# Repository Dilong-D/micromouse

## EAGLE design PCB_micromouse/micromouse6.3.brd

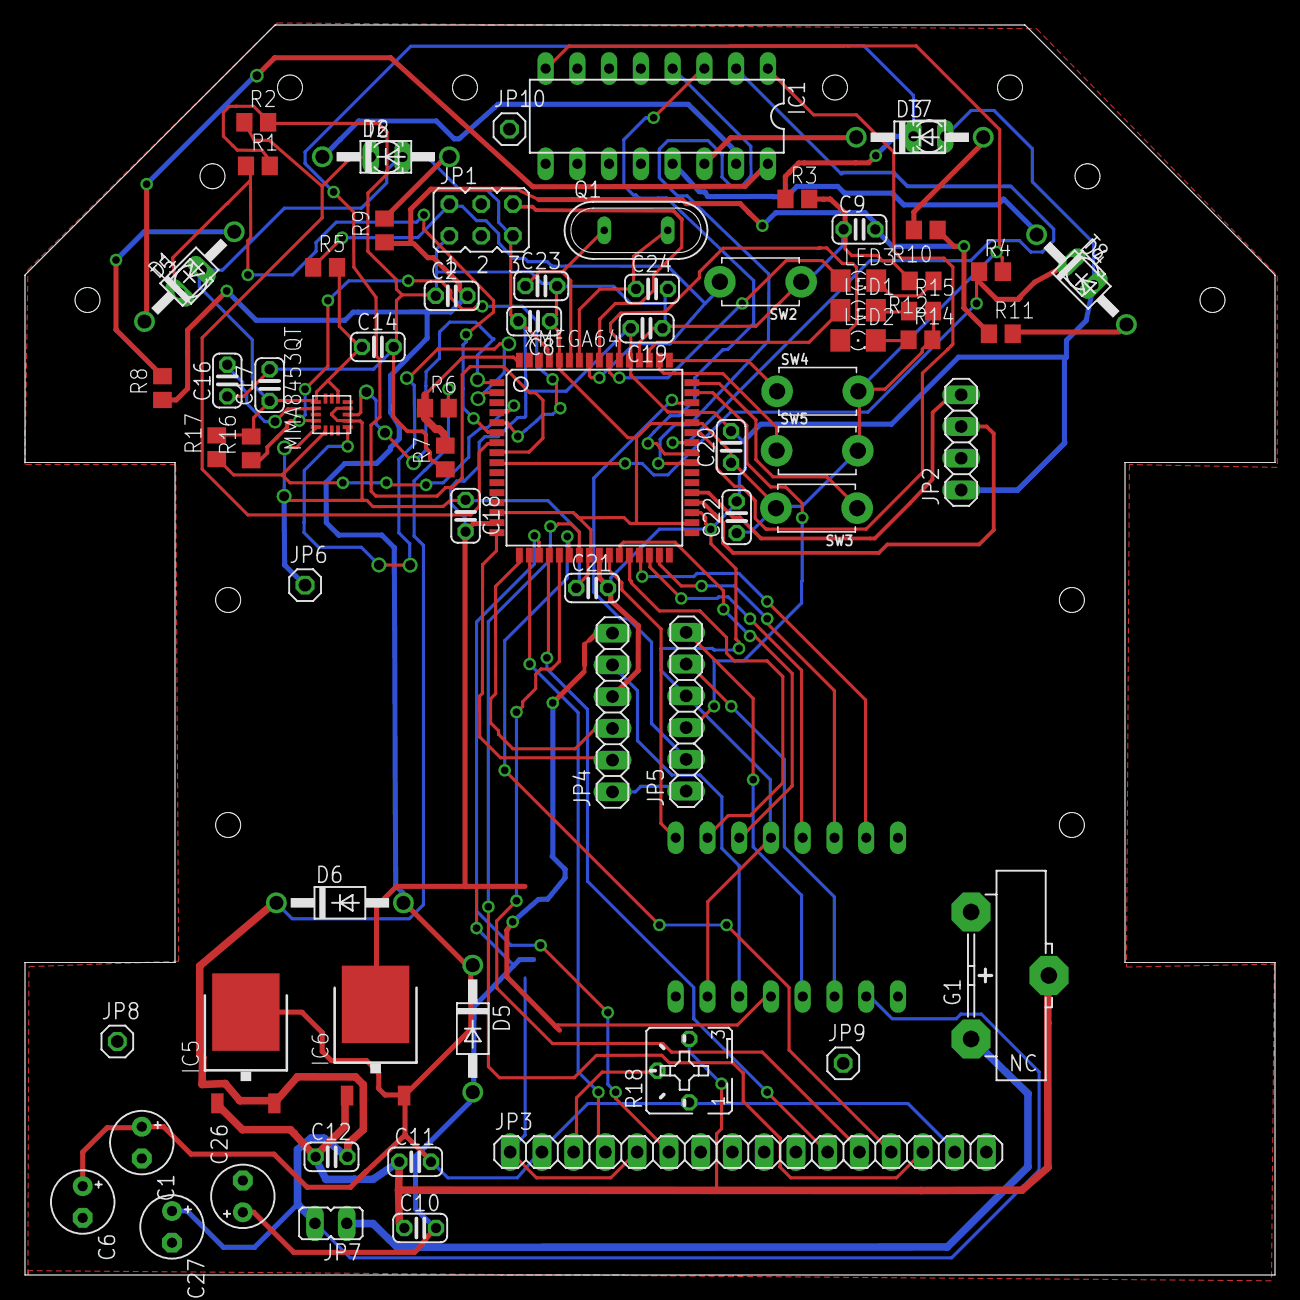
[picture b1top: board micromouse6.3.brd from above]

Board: 2 copper layers, 100.0 x 100.0 mm, 72 parts (0 on the bottom side), 63 nets.

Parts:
ACC1: MMA8453QT
C1, C6, C26, C27: E2,5-5
C2, C9: C025-024X044
C8, C11, C12, C18, C19, C20, C21, C22: 100n; C025-024X044
C10: 10μ; C025-024X044
C14: 4,7μ; C025-024X044
C16, C17: 0.1μ; C025-024X044
C23, C24: 15p; C025-024X044
D1, D2, D3, D4: sfh4550; DO41-10
D5, D6: 1N4004; DO41-10
G1: 1V60R
IC1: ULN2003AN; DIL16
IC5, IC6: LM1117IDTX-3.3; TO252
JP1: JP3Q
JP2: 1X04
JP3: 1X16
JP4, JP5: 1X06
JP6, JP8, JP9, JP10: 1X01
JP7: JP1
LED1, LED2, LED3: 1206
Q1: QS
R1, R2, R3, R4: 1k; R0805
R5, R7: 10k; R0805
R6: 20k; R0805
R8, R9, R10, R11: 10; R0805
R12, R14, R15: 220; R0805
R16, R17: 4.7k; R0805
R18: B25P
SW2, SW3, SW4, SW5: TACT_PANA-EVQ
T5, T6, T7, T8: BPX81
U$1: POLULU713
XMEGA64: TQFP64

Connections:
AIN: R6.1, R7.2, XMEGA64.64
A_IN1: U$1.P$14, XMEGA64.27
A_IN2: U$1.P$15, XMEGA64.28
A_PWM: U$1.P$16, XMEGA64.26
B_IN1: U$1.P$12, XMEGA64.30
B_IN2: U$1.P$11, XMEGA64.31
B_PWM: U$1.P$10, XMEGA64.29
CLK: JP1.2, R5.1, SW2.P$2, XMEGA64.57
CLK_: JP2.3, XMEGA64.36
DATA: JP1.6, XMEGA64.56
FOTRA1: R1.1, T5.E, XMEGA64.6
FOTRA2: R2.1, T6.E, XMEGA64.7
FOTRA3: R3.1, T7.E, XMEGA64.8
FOTRA4: R4.1, T8.E, XMEGA64.9
GND: ACC1.GND1, ACC1.GND2, ACC1.GND3, C1.-, C2.1, C6.-, C8.1, C9.1, C10.1, C11.1, C12.1, C14.2, C16.1, C17.2, C18.1, C19.1, C20.1, C21.1, C22.1, C23.2, C24.2, C26.-, C27.-, G1.-, IC1.8, IC5.1, IC6.1, JP1.1, JP2.2, JP3.1, JP3.5, JP3.16, JP4.1, JP5.1, JP6.1, JP8.1, JP9.1, JP10.1, R1.2, R2.2, R3.2, R4.2, R7.1, R12.2, R14.2, R15.2, R18.E, SW2.P$1, SW3.P$2, SW4.P$2, SW5.P$2, U$1.P$1, U$1.P$8, U$1.P$9, XMEGA64.14, XMEGA64.24, XMEGA64.34, XMEGA64.44, XMEGA64.52, XMEGA64.60
INT1: ACC1.INT1, XMEGA64.1
INT2: ACC1.INT2, XMEGA64.2
L_DIAG: IC1.1, XMEGA64.43
L_FROM: IC1.2, XMEGA64.42
MA_OUT1: JP4.5, U$1.P$3
MA_OUT2: JP4.6, U$1.P$4
MB_OUT1: JP5.5, U$1.P$6
MB_OUT2: JP5.6, U$1.P$5
unnamed: LED1.A, XMEGA64.51
unnamed: D2.A, R9.2
unnamed: D1.A, R8.2
unnamed: D1.C, IC1.16
unnamed: D2.C, IC1.15
unnamed: D4.A, R11.2
unnamed: D3.C, IC1.14
unnamed: D3.A, R10.2
unnamed: D4.C, IC1.13
unnamed: LED2.A, XMEGA64.54
unnamed: JP3.13, XMEGA64.22
unnamed: JP3.4, XMEGA64.18
unnamed: JP3.6, XMEGA64.19
unnamed: LED3.A, XMEGA64.55
unnamed: C23.1, Q1.1, XMEGA64.59
unnamed: SW3.P$1, XMEGA64.48
unnamed: G1.+, JP7.1
unnamed: JP3.3, R18.S
unnamed: C24.1, Q1.2, XMEGA64.58
unnamed: SW4.P$1, XMEGA64.49
unnamed: SW5.P$1, XMEGA64.50
unnamed: JP3.11, XMEGA64.20
unnamed: LED3.C, R12.1
unnamed: LED2.C, R14.1
unnamed: LED1.C, R15.1
unnamed: JP2.4, XMEGA64.37
unnamed: ACC1.BYP, C16.2
unnamed: JP3.12, XMEGA64.21
unnamed: JP3.14, XMEGA64.23
OUTA1: JP4.2, XMEGA64.16
OUTA2: JP4.3, XMEGA64.17
OUTB1: JP5.2, XMEGA64.46
OUTB2: JP5.3, XMEGA64.47
R_DIAG: IC1.3, XMEGA64.41
R_FRONT: IC1.4, XMEGA64.40
SCL: ACC1.SCL, R16.1, XMEGA64.5
SDA: ACC1.SDA, R17.1, XMEGA64.4
VCC3: ACC1.VDD, ACC1.VDDIO, C8.2, C10.2, C14.1, C17.1, C18.2, C19.2, C20.2, C21.2, C22.2, C26.+, D5.A, IC6.TAB, JP1.5, JP2.1, JP4.4, JP5.4, R5.2, R16.2, R17.2, T5.C, T6.C, T7.C, T8.C, U$1.P$2, U$1.P$13, XMEGA64.15, XMEGA64.25, XMEGA64.35, XMEGA64.45, XMEGA64.53, XMEGA64.61
VCC5: C1.+, C2.2, C6.+, C9.2, C11.2, D5.C, D6.A, IC5.TAB, IC6.2, JP3.2, JP3.15, R8.1, R9.1, R10.1, R11.1, R18.A
VCC7: C12.2, C27.+, D6.C, IC5.2, JP7.2, R6.2, U$1.P$7

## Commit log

2017-07-27 MATLAB: skrypty do odczytu bluetoothKod:Micromouse jezdzi, pozycjonuje sie wzgledem scianek i porusza algorytmem lewej reki
2017-07-27 MATLAB: skrypty do odczytu bluetooth, PCB_MICROMOUSE: projekty PCB, KOD:Micromouse jezdzi, pozycjonuje sie wzgledem scianek i porusza algorytmem lewej reki
2017-08-09 Kod Artura i Janka do merge
2017-08-09 Uzupelnienie kodu - polaczenie algorytmu z rzeczywistoscia
2017-08-09 kod artura i janka
2017-08-09 bluetooth added
2017-08-09 sdfhgsdfghs
2017-08-09 zmiana step_forward_real - wiecej pomiarow
2017-08-09 ploting lab
2017-08-09 praca nad pomiarami
2017-08-09 praca nad pomiarami2
